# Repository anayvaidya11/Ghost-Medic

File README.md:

# Archiater

*A **Wyzantium Industries** project. Formerly Ghost Medic; renamed 2026-08-05.*

**Offline decision-support software for the trained responder, running on the
device they already carry, with an optional wrist sensor accessory streaming
raw signals into it.** A local language model reasons about the patient, the
environment, and what the responder says, and speaks numbered candidate
actions. The responder on scene decides. No network, ever.

It is built for the places where help is hours away and there is no signal —
which is precisely where every other assistant stops working, because they all
assume a network. The gap it aims at sits between a satellite messenger, which
can reach help but cannot tell you what to do, and a printed
wilderness-medicine manual, which knows what to do but cannot see your
situation. (Why the product is software-first, and what that decision killed:
[`docs/POSITIONING.md`](docs/POSITIONING.md).)

The full system: 

```
  ┌───────────────────────┐                 ┌─────────────────────────────────┐
  │  1. WRIST SENSOR      │    JSON over    │  2. END-USER DEVICE             │
  │  ACCESSORY (optional) │ ── USB serial ─▶│  the responder's phone / laptop │──▶ responder
  │  RP2040 hub,          │   (raw signal + │  local LLM + voice + screen app │    decides
  │  3 sensors            │    environment) │  (React Native / Expo, Ollama)  │
  └───────────────────────┘                 └─────────────────────────────────┘
     firmware/                                 services/ + app/ (this repo)
```

## The parts

### 1. Wrist sensor accessory — optional hub  → [`firmware/`](firmware/)
A **Raspberry Pi Pico / RP2040** reading three I²C sensors on a shared bus:

| Sensor   | Role                                   |
|----------|----------------------------------------|
| MAX30102 | Raw optical (PPG) front-end — raw red/IR counts, **not** HR/SpO₂ |
| BMP280   | Barometric pressure → altitude         |
| LIS3DH   | Accelerometer → motion / fall detection |

It samples at 10 Hz and streams one JSON object per line over USB serial. The
firmware is bare-metal C written against the Raspberry Pi Pico SDK. See
[`firmware/README.md`](firmware/README.md) for the driver details and, importantly,
the **honest validation status** (summarized below).

>  The firmware is **written and
> compile-tested against the real Raspberry Pi Pico SDK** It has
> **NOT yet been flashed or run on physical hardware**, and its readings have not
> been checked against real sensors. The drivers were transcribed carefully from
> the MAX30102, BMP280, LIS3DH datasheets, but transcription and timing bugs can
> only be caught on a bench, which hasn't happened yet. Treat it as a
> compile-verified design artifact. Full detail and
> the reasoning (including why no simulator run) is in
> [`firmware/README.md`](firmware/README.md).

### 2. The end-user device — app + local LLM  → [`services/`](services/)
The responder's own phone, EUD, or laptop, running a **local, off-the-shelf**
language model that consumes the sensor stream plus the responder's input and
produces decision support — all offline.

**This works today** (verified 2026-07-22): the app sends its prompt plus a
sensor-context block to `llama3.2:3b` running under Ollama on the same machine,
and the sensor state measurably changes the guidance — a fall flag adds head,
neck and spine assessment that the same question without it does not produce.
Evidence: [`docs/session-reports/2026-07-22-phase2-sensor-aware-llm.md`](docs/session-reports/2026-07-22-phase2-sensor-aware-llm.md).

**No dedicated compute unit will be built.** The end-user device is the
compute (decision 2026-08-05, [`docs/POSITIONING.md`](docs/POSITIONING.md)).
A laptop stands in for that device in the demo — and a laptop *is* an
end-user device, which is the point.

### 3. Interface — voice + screen app  → repo root (this repo)
The **React Native / Expo** app is the voice and screen surface the user actually
interacts with. It lives directly at the repository root rather than in a single
subfolder:

| Path                | What's there                         |
|---------------------|--------------------------------------|
| [`app/`](app/)      | expo-router app — entry (`_layout.tsx`) + the UI (`index.tsx`) |
| [`services/`](services/) | LLM plumbing + forward-looking sensor/vision stubs |
| [`training/`](training/) | Fine-tuning pipeline — see [`training/README.md`](training/README.md) |

## Start here (project docs)

| Doc | What it's for |
|---|---|
| [`ROADMAP.md`](ROADMAP.md) | **Read first.** Phased plan + what's done vs. next. |
| [`ARCHITECTURE.md`](ARCHITECTURE.md) | System topology, what runs where, real-vs-simulated table. |
| [`DATA_FORMAT.md`](DATA_FORMAT.md) | The NDJSON wire contract between firmware, bridge, and app. |
| [`docs/POSITIONING.md`](docs/POSITIONING.md) | Why the product was repositioned 2026-08-05. Read this to understand the current framing. |

## Repository layout

```
Archiater/
├── README.md            ← you are here (whole-system overview)
├── ROADMAP.md · ARCHITECTURE.md · DATA_FORMAT.md   ← project memory
├── firmware/            ← 1. wrist sensor accessory — RP2040 hub (Pico SDK C)
│   └── README.md          firmware detail + validation status
├── simulator/           ← browser demo emitting firmware-format JSON (hardware-free)
├── app/                 ← 3. interface — React Native / Expo app (the entry)
├── services/            ← LLM + sensor/vision service layer
├── training/            ← wilderness-medicine fine-tuning pipeline
├── legacy/              ← archived deterministic TCCC app (not the product)
├── app.json, package.json, tsconfig.json, babel.config.js
└── ...
```

The **product is the offline decision-support software** (`app/` + `services/`). An earlier
deterministic TCCC/MARCH engine lives in [`legacy/`](legacy/README.md) — archived,
not deleted, and not imported by anything shipping.

## Data flow, in one sentence

The wrist accessory emits JSON sensor lines over USB serial → a serial→WebSocket
bridge forwards them to the app → the app pairs them with the responder's voice
input and the local LLM's reasoning to give offline decision support.

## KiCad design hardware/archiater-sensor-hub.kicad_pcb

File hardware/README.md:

# Archiater — Wrist-Unit PCB (hardware/)

KiCad **10.0.4** design for the Archiater wrist-unit sensor hub — the custom
board referenced throughout the docs. This is the real design source, committed so
the "custom PCB" claim is backed by files you can open, not just a screenshot.

> ## ⚠️ Honest status
> This board is **designed and routed in KiCad — not fabricated, not assembled,
> and not bench-tested.** No copy of this PCB physically exists yet. The firmware
> (`../firmware/`) is separately compile-verified against the Pico SDK but has also
> **never been run on this board.** Treat this as a verified *design artifact*: a
> complete schematic + routed 2-layer layout, with pin assignments that match the
> firmware — not a manufactured product.

## What's here

| File | What it is |
|---|---|
| `archiater-sensor-hub.kicad_sch` | Schematic (source of truth for the wiring) |
| `archiater-sensor-hub.kicad_pcb` | Routed board layout (35 footprints, ~477 track segments) |
| `archiater-sensor-hub.kicad_pro` | KiCad project file |
| `exports/archiater-sensor-hub-schematic.pdf` | Schematic, exported for viewing without KiCad |
| `exports/archiater-sensor-hub-3d-top.png` | 3D board render (KiCad 3D viewer, top) — the still fallback on the website |
| `exports/archiater-sensor-hub.glb` | 3D board model for the website's interactive viewer |
| `exports/archiater-sensor-hub-front-copper.svg` | Front copper layer as 2D artwork |

The `exports/` images are **generated from the source in this folder** — see
"Regenerating the images" below. They are the design's own tool output, not photos:
no physical board exists to photograph (see status above).

## The design

A single-board wrist unit: an RP2040 reading three I²C sensors, powered/programmed
over USB-C.

| Ref | Part | Role |
|---|---|---|
| U3 | RP2040 | MCU (bare-metal firmware, `../firmware/`) |
| U1 | W25Q128JVS | QSPI flash (firmware storage) |
| U2 | AMS1117-3.3 | 5 V (USB VBUS) → 3.3 V regulator |
| U4 | MAX30102 | **Raw optical (PPG) front-end — raw red/IR counts, not HR/SpO₂** |
| U6 | BMP280 | Barometric pressure / temperature → altitude |
| U5 | LIS3DH | 3-axis accelerometer → motion / fall detection |
| J1 | USB-C 2.0 (16P) | Power + data |
| Y1 | 12 MHz crystal | RP2040 clock |
| R6, R7 | 4.7 kΩ | I²C SDA/SCL pull-ups (shared bus) |
| SW1, SW2 | Push buttons | RUN / BOOT |
| D1 | LED | Status |

The three sensors share **one I²C bus** with a single pull-up pair (R6/R7) — the
same shared-bus topology described in `../README.md` and `../DATA_FORMAT.md`. The
MAX30102 label here matches the rest of the repo: it is a **raw optical front-end**,
and the firmware exposes raw red/IR counts, **not** a computed heart rate or SpO₂.

## Regenerating the exports

Everything in `exports/` is reproducible from the source in this folder with
KiCad 10.x. `kicad-cli` ships inside KiCad — on macOS it lives at
`/Applications/KiCad/KiCad.app/Contents/MacOS/kicad-cli`, which is not on `PATH`
by default:

```sh
KC=/Applications/KiCad/KiCad.app/Contents/MacOS/kicad-cli

# 1 — schematic PDF
$KC sch export pdf archiater-sensor-hub.kicad_sch \
  -o exports/archiater-sensor-hub-schematic.pdf

# 2 — still 3D render (the website's fallback when WebGL is unavailable)
$KC pcb render archiater-sensor-hub.kicad_pcb \
  -o exports/archiater-sensor-hub-3d-top.png --side top --quality high

# 3 — 3D model for the website's interactive viewer
$KC pcb export glb archiater-sensor-hub.kicad_pcb \
  -o exports/archiater-sensor-hub.glb --force \
  --include-silkscreen --include-soldermask

# 4 — front copper as 2D artwork (black on transparent)
$KC pcb export svg archiater-sensor-hub.kicad_pcb \
  -o exports/archiater-sensor-hub-front-copper.svg \
  --layers F.Cu,Edge.Cuts --mode-single --exclude-drawing-sheet \
  --fit-page-to-board --black-and-white
```

Then copy the four outputs into `../site/assets/`.

Or open `archiater-sensor-hub.kicad_pro` in KiCad and use **View → 3D Viewer**.

### Notes on those choices, so they aren't silently re-litigated

- **GLB, not VRML or STEP.** `kicad-cli` can emit all three; GLB is binary glTF,
  which three.js loads natively via `GLTFLoader` with materials intact and no
  conversion step.
- **Silkscreen and soldermask only — no `--include-tracks/-pads/-zones`.** Adding
  those triples the file (1.8 MB → 6.1 MB) and quadruples the draw calls for
  geometry you cannot see: the soldermask renders opaque, so the copper is hidden
  in the 3D view exactly as it is on a real board. Export 4 above is how the
  routing is actually shown.
- **One model is missing.** The MAX30102's package (`Maxim_OLGA-14_3.3x5.6mm_P0.8mm`)
  has no STEP model in the standard library, so U4 has no body in the render and
  `kicad-cli` prints `File not found:` for it. The part is present in the
  schematic and routed on the board; only its 3D shape is absent. The website
  says so rather than substituting a stand-in shape.

## Where this sits in the project

Hardware is **not** on the current critical path — see `../ROADMAP.md` (the wired
bridge stands in for the board today, and PCB *fabrication* is explicitly deferred).
This folder exists so the design work is visible and verifiable now.

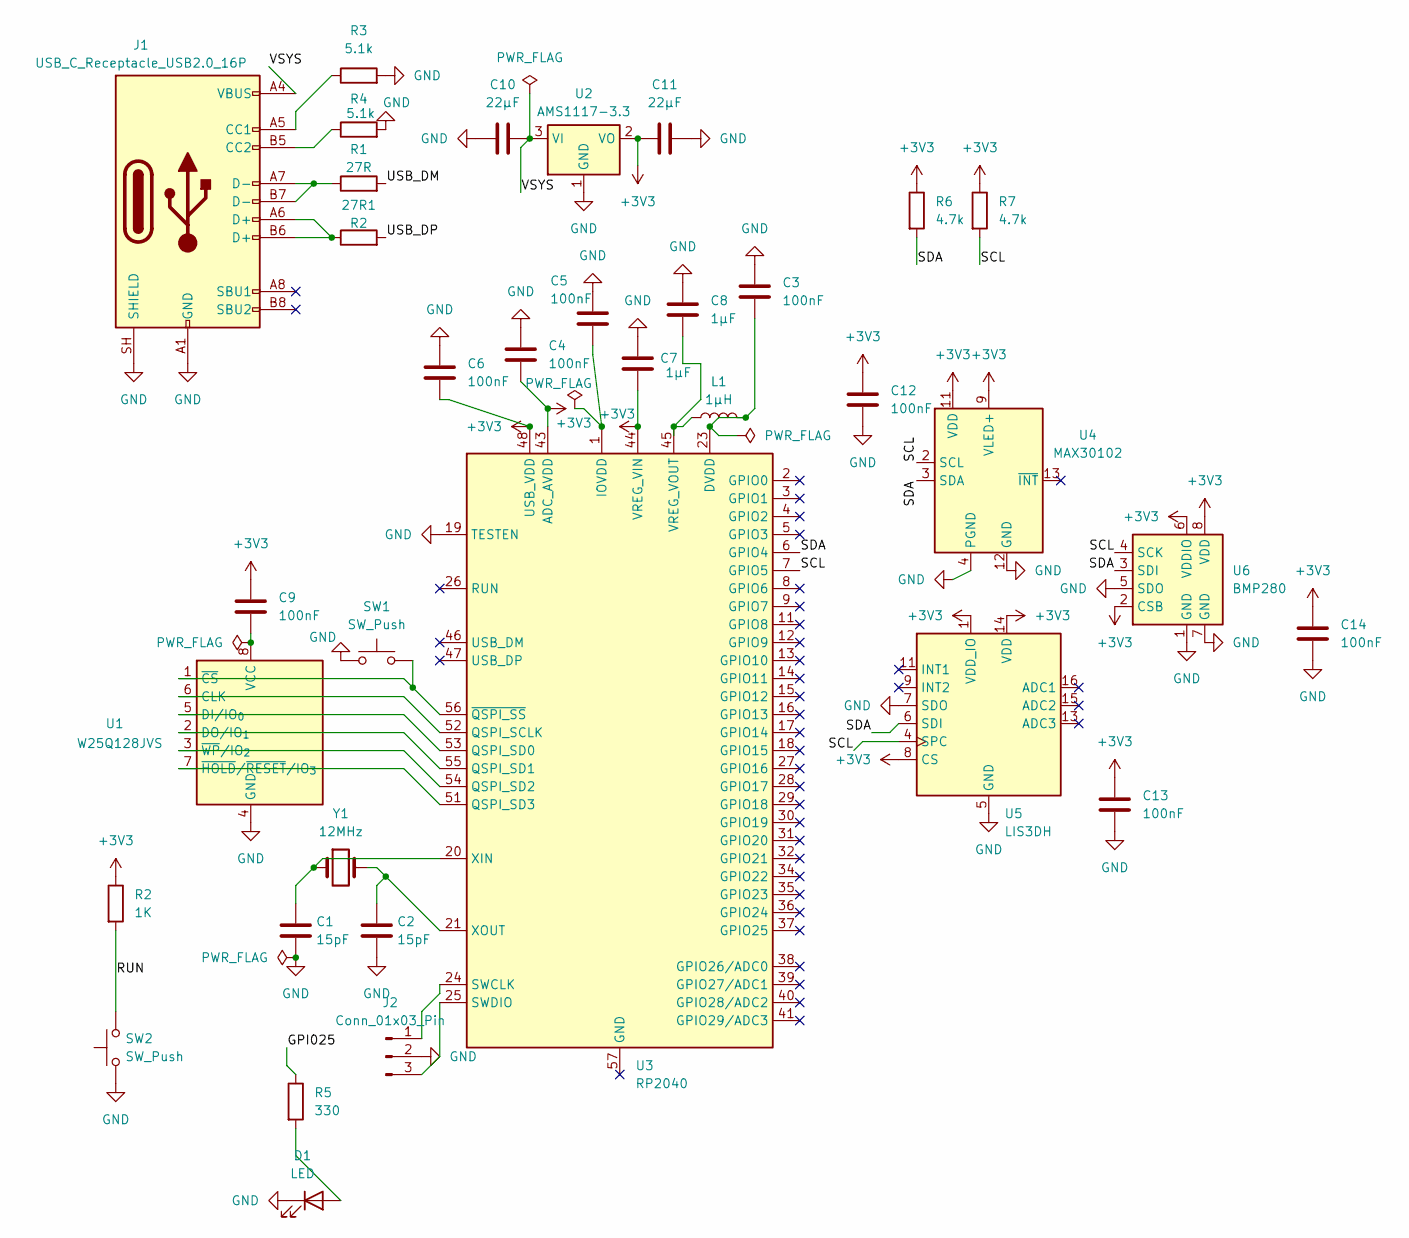
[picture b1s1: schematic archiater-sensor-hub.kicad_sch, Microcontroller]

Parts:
27R1: R2; R_0805_2012Metric
C1, C2: 15pF; C_0805_2012Metric
C3, C4, C5, C6, C9, C12, C13, C14: 100nF; C_0805_2012Metric
C7, C8: 1µF; C_0805_2012Metric
C10, C11: 22µF; C_0805_2012Metric
D1: LED; LED_0805_2012Metric
J1: USB_C_Receptacle_USB2.0_16P; USB_C_Receptacle_GCT_USB4105-xx-A_16P_TopMnt_Horizontal
J2: Conn_01x03_Pin; PinHeader_1x03_P2.54mm_Vertical
L1: 1µH; L_0805_2012Metric
R1: 27R; R_0805_2012Metric
R2: 1K; R_0805_2012Metric
R3, R4: 5.1k; R_0805_2012Metric
R5: 330; R_0805_2012Metric
R6, R7: 4.7k; R_0805_2012Metric
SW1, SW2: SW_Push; SW_SPST_TL3342
U1: W25Q128JVS; SOIC-8_5.3x5.3mm_P1.27mm
U2: AMS1117-3.3; SOT-223-3_TabPin2
U3: RP2040; QFN-56-1EP_7x7mm_P0.4mm_EP3.2x3.2mm
U4: MAX30102; Maxim_OLGA-14_3.3x5.6mm_P0.8mm
U5: LIS3DH; LGA-16_3x3mm_P0.5mm_LayoutBorder3x5y
U6: BMP280; Bosch_LGA-8_2x2.5mm_P0.65mm_ClockwisePinNumbering
Y1: 12MHz; Crystal_SMD_3215-2Pin_3.2x1.5mm

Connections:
+3V3: C4.2, C6.2, C7.2, C9.2, C11.2, C12.1, C13.1, C14.1, R2.1, R6.1, R7.1, U2.2 (VO), U3.43 (ADC_AVDD), U3.44 (VREG_VIN), U3.48 (USB_VDD), U4.9 (VLED+), U4.10 (VLED+), U4.11 (VDD), U5.1 (VDD_IO), U5.8 (CS), U5.14 (VDD), U6.2 (CSB), U6.6 (VDDIO), U6.8 (VDD)
/GPI025: R5.1
/RUN: R2.2, SW2.2
/SCL: R7.2, U3.7 (GPIO5), U4.2 (SCL), U5.4 (SPC), U6.4 (SCK)
/SDA: R6.2, U3.6 (GPIO4), U4.3 (SDA), U5.6 (SDI), U6.3 (SDI)
/USB_DM: R1.2
/USB_DP: 27R1.2
/VSYS: C10.1, J1.A4 (VBUS), J1.A9 (VBUS), J1.B4 (VBUS), J1.B9 (VBUS), U2.3 (VI)
GND: C1.2, C2.2, C3.1, C4.1, C5.1, C6.1, C7.1, C8.1, C10.2, C11.1, C12.2, C13.2, C14.2, D1.1 (K), J1.A1 (GND), J1.A12 (GND), J1.B1 (GND), J1.B12 (GND), J1.SH (SHIELD), J2.2, R3.2, R4.2, SW1.1, SW2.1, U1.4 (GND), U2.1 (GND), U3.19 (TESTEN), U4.4 (PGND), U4.12 (GND), U5.5 (GND), U5.7 (SDO), U5.10 (GND), U5.12 (GND), U6.1 (GND), U6.5 (SDO), U6.7 (GND)
unnamed: 27R1.1, J1.A6 (D+), J1.B6 (D+)
unnamed: C3.2, L1.2, U3.23 (DVDD), U3.50 (DVDD)
unnamed: C5.2, U3.1 (IOVDD), U3.10 (IOVDD), U3.22 (IOVDD), U3.33 (IOVDD), U3.42 (IOVDD), U3.49 (IOVDD)
unnamed: D1.2 (A), R5.2
unnamed: J1.A5 (CC1), R3.1
unnamed: J1.B5 (CC2), R4.1
unnamed: J1.A7 (D-), J1.B7 (D-), R1.1
unnamed: J2.1, U3.24 (SWCLK)
unnamed: J2.3, U3.25 (SWDIO)
unnamed: U1.6 (CLK), U3.52 (QSPI_SCLK)
unnamed: U1.5 (DI/IO_{0}), U3.53 (QSPI_SD0)
unnamed: U1.2 (DO/IO_{1}), U3.55 (QSPI_SD1)
unnamed: C9.1, U1.8 (VCC)
unnamed: SW1.2, U1.1 (~CS), U3.56 (~QSPI_SS)
unnamed: U1.7 (~HOLD/~RESET/IO_{3}), U3.51 (QSPI_SD3)
unnamed: U1.3 (~WP/IO_{2}), U3.54 (QSPI_SD2)
unnamed: C8.2, L1.1, U3.45 (VREG_VOUT)
unnamed: C1.1, U3.20 (XIN), Y1.1
unnamed: C2.1, U3.21 (XOUT), Y1.2

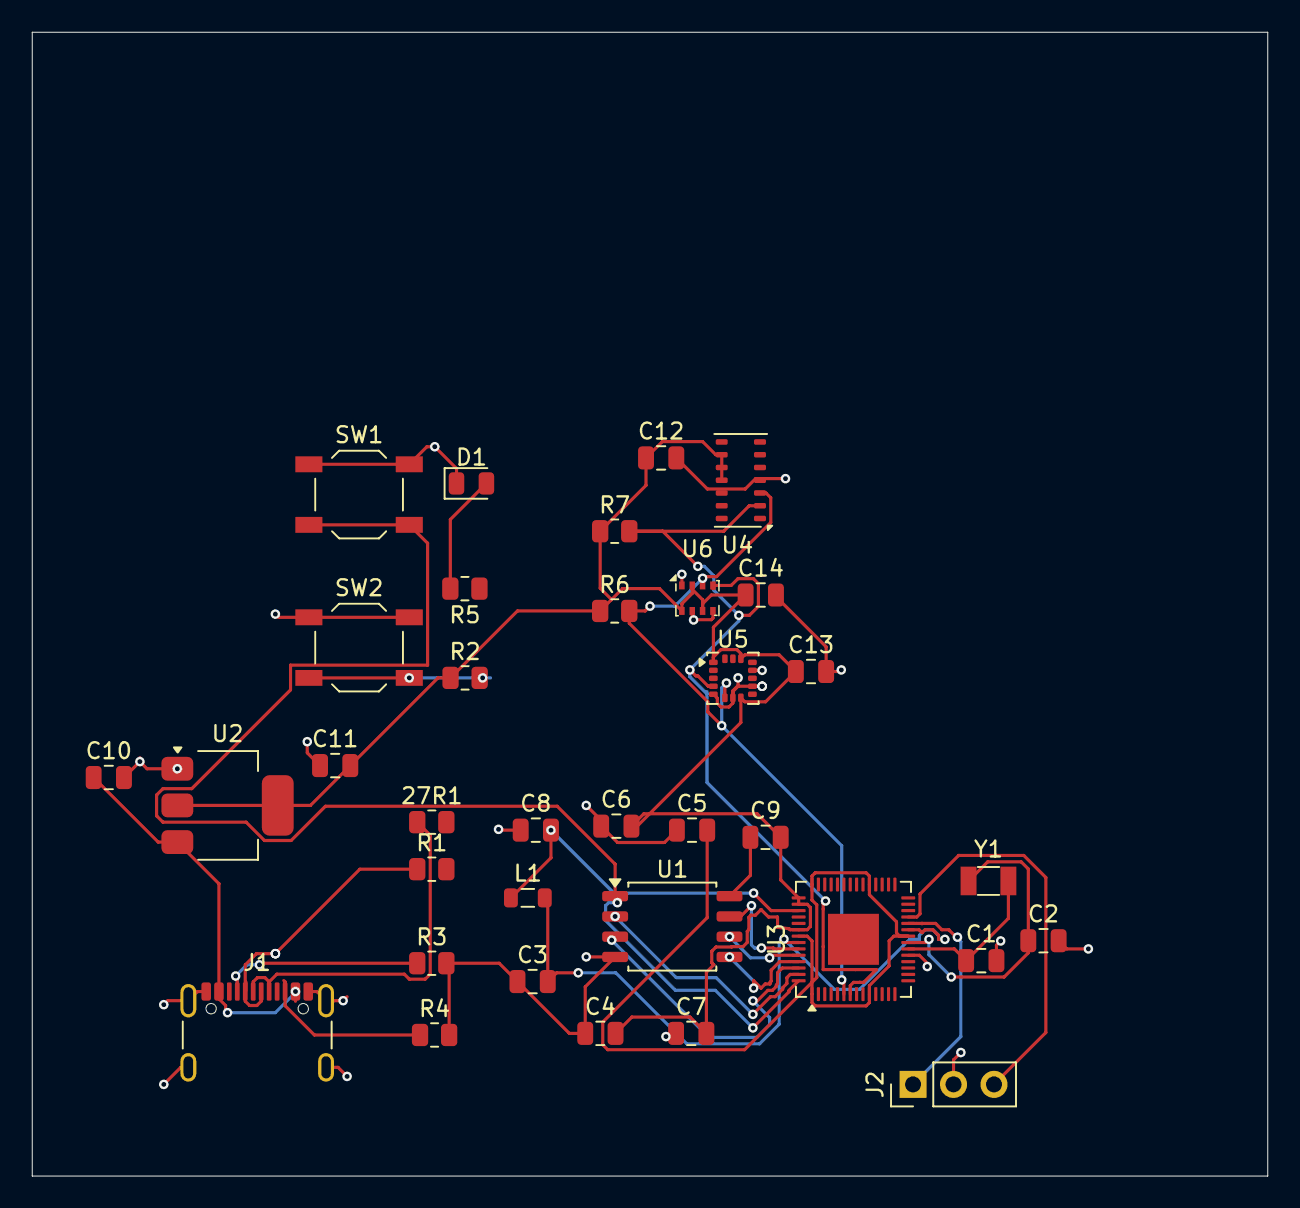
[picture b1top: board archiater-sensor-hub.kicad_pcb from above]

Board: 2 copper layers, 77.5 x 71.8 mm, 35 parts (0 on the bottom side), 25 nets.

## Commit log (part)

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2026-05-29 Add TypeScript config, theme, types, and scenario files; update package.json and babel for expo-router migration
    https://claude.ai/code/session_01TRjxcjzUT1yDFs12uGi9WH
2026-05-29 Merge Jonathan+Anay repos: TypeScript, expo-router, Zustand, MARCH protocol, SILENT mode, biosensor stub, LLM streaming
    - Migrated full codebase to TypeScript + expo-router (app/ directory)
    - app/index.tsx: MODE SELECT (SELF-AID / BUDDY-AID / SILENT)
    - app/triage.tsx: concern tiles, wound photo (expo-image-picker), voice recording (expo-audio), biosensor vitals bar
    - app/vitals.tsx: manual entry + live biosensor readouts when connected
    - app/action.tsx: MARCH step-by-step execution + AIResponse + LLM transmit input
    - app/mist.tsx: auto-filled MIST handoff card from session data
2026-06-25 wilderness SAR pivot
